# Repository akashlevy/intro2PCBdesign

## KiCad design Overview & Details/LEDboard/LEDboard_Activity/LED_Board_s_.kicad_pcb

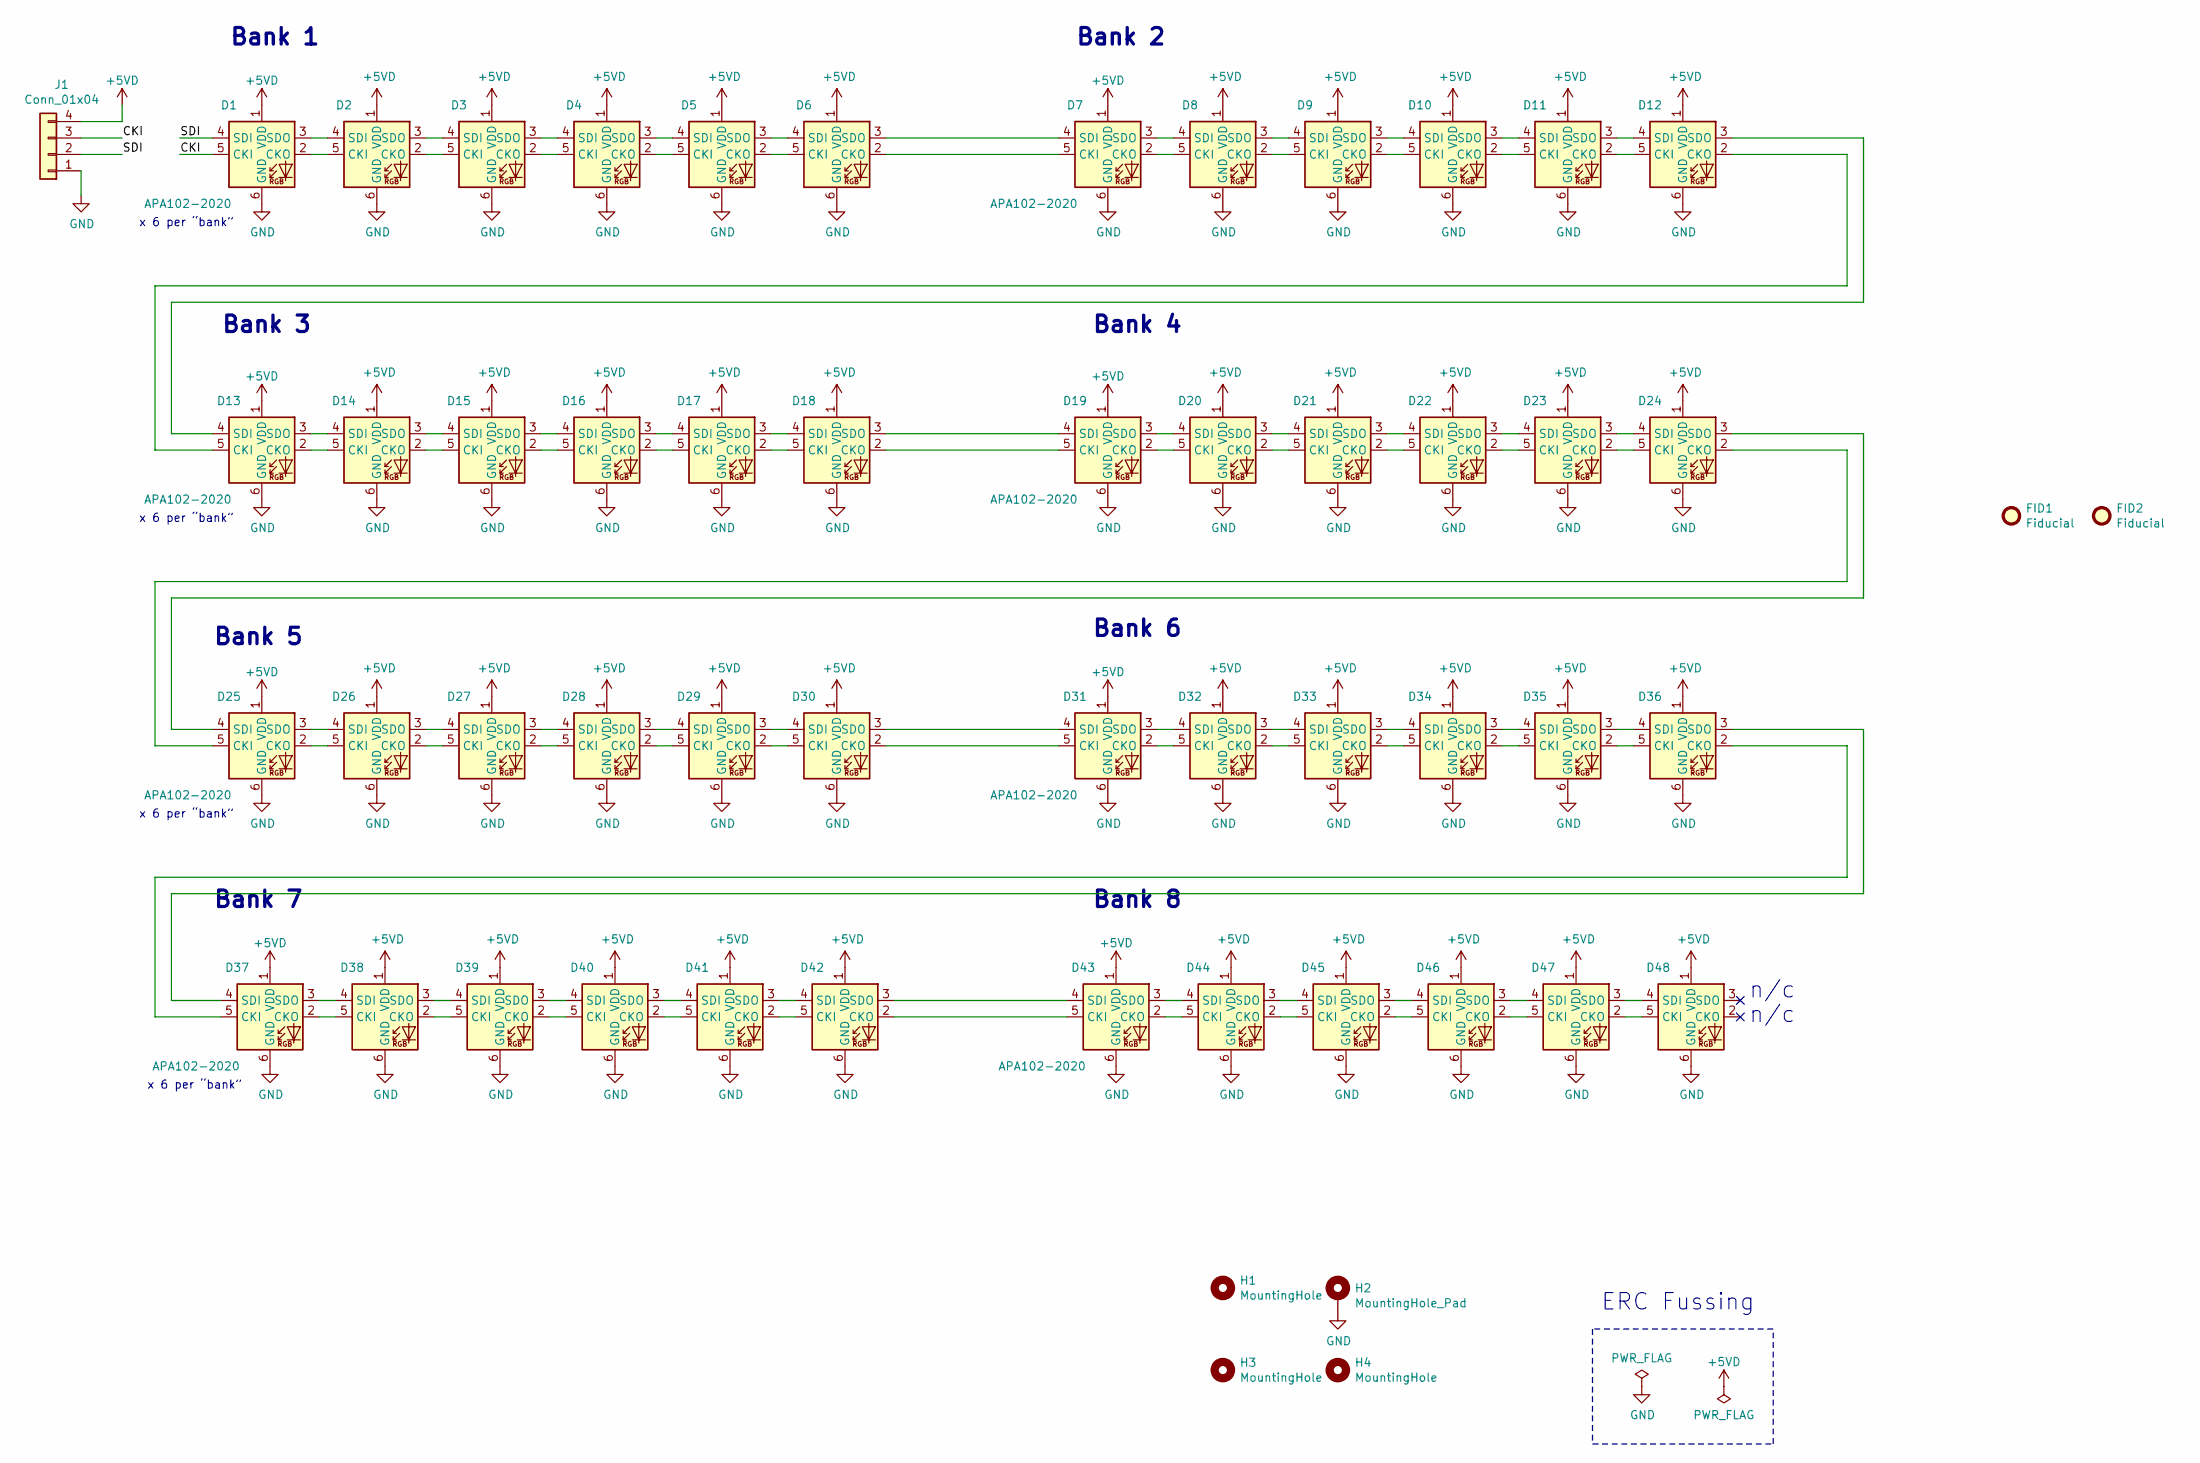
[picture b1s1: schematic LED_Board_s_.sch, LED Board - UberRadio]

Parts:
D1, D2, D3, D4, D5, D6, D7, D8, D9, D10, D11, D12, D13, D14, D15, D16, D17, D18, D19, D20, D21, D22, D23, D24, D25, D26, D27, D28, D29, D30, D31, D32, D33, D34, D35, D36, D37, D38, D39, D40, D41, D42, D43, D44, D45, D46, D47, D48: APA102-2020; LED-APA102-2020
FID1, FID2: Fiducial; Fiducial_0.5mm_Mask1mm
H1, H3, H4: MountingHole; MountingHole_3.5mm_Pad
H2: MountingHole_Pad; MountingHole_3.5mm_Pad_Via
J1: Conn_01x04; PinHeader_1x04_P2.54mm_Vertical

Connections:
+5VD: D1.1 (VDD), D2.1 (VDD), D3.1 (VDD), D4.1 (VDD), D5.1 (VDD), D6.1 (VDD), D7.1 (VDD), D8.1 (VDD), D9.1 (VDD), D10.1 (VDD), D11.1 (VDD), D12.1 (VDD), D13.1 (VDD), D14.1 (VDD), D15.1 (VDD), D16.1 (VDD), D17.1 (VDD), D18.1 (VDD), D19.1 (VDD), D20.1 (VDD), D21.1 (VDD), D22.1 (VDD), D23.1 (VDD), D24.1 (VDD), D25.1 (VDD), D26.1 (VDD), D27.1 (VDD), D28.1 (VDD), D29.1 (VDD), D30.1 (VDD), D31.1 (VDD), D32.1 (VDD), D33.1 (VDD), D34.1 (VDD), D35.1 (VDD), D36.1 (VDD), D37.1 (VDD), D38.1 (VDD), D39.1 (VDD), D40.1 (VDD), D41.1 (VDD), D42.1 (VDD), D43.1 (VDD), D44.1 (VDD), D45.1 (VDD), D46.1 (VDD), D47.1 (VDD), D48.1 (VDD), J1.4
/CKI: D1.5 (CKI), J1.3
/SDI: D1.4 (SDI), J1.2
GND: D1.6 (GND), D2.6 (GND), D3.6 (GND), D4.6 (GND), D5.6 (GND), D6.6 (GND), D7.6 (GND), D8.6 (GND), D9.6 (GND), D10.6 (GND), D11.6 (GND), D12.6 (GND), D13.6 (GND), D14.6 (GND), D15.6 (GND), D16.6 (GND), D17.6 (GND), D18.6 (GND), D19.6 (GND), D20.6 (GND), D21.6 (GND), D22.6 (GND), D23.6 (GND), D24.6 (GND), D25.6 (GND), D26.6 (GND), D27.6 (GND), D28.6 (GND), D29.6 (GND), D30.6 (GND), D31.6 (GND), D32.6 (GND), D33.6 (GND), D34.6 (GND), D35.6 (GND), D36.6 (GND), D37.6 (GND), D38.6 (GND), D39.6 (GND), D40.6 (GND), D41.6 (GND), D42.6 (GND), D43.6 (GND), D44.6 (GND), D45.6 (GND), D46.6 (GND), D47.6 (GND), D48.6 (GND), H2.1, H3.1, J1.1
unnamed: D1.2 (CKO), D2.5 (CKI)
unnamed: D1.3 (SDO), D2.4 (SDI)
unnamed: D2.2 (CKO), D3.5 (CKI)
unnamed: D2.3 (SDO), D3.4 (SDI)
unnamed: D3.2 (CKO), D4.5 (CKI)
unnamed: D3.3 (SDO), D4.4 (SDI)
unnamed: D4.2 (CKO), D5.5 (CKI)
unnamed: D4.3 (SDO), D5.4 (SDI)
unnamed: D5.2 (CKO), D6.5 (CKI)
unnamed: D5.3 (SDO), D6.4 (SDI)
unnamed: D6.2 (CKO), D7.5 (CKI)
unnamed: D6.3 (SDO), D7.4 (SDI)
unnamed: D7.2 (CKO), D8.5 (CKI)
unnamed: D7.3 (SDO), D8.4 (SDI)
unnamed: D8.2 (CKO), D9.5 (CKI)
unnamed: D8.3 (SDO), D9.4 (SDI)
unnamed: D10.2 (CKO), D11.5 (CKI)
unnamed: D10.3 (SDO), D11.4 (SDI)
unnamed: D9.3 (SDO), D10.4 (SDI)
unnamed: D9.2 (CKO), D10.5 (CKI)
unnamed: D11.2 (CKO), D12.5 (CKI)
unnamed: D11.3 (SDO), D12.4 (SDI)
unnamed: D12.2 (CKO), D13.5 (CKI)
unnamed: D12.3 (SDO), D13.4 (SDI)
unnamed: D13.2 (CKO), D14.5 (CKI)
unnamed: D13.3 (SDO), D14.4 (SDI)
unnamed: D14.2 (CKO), D15.5 (CKI)
unnamed: D14.3 (SDO), D15.4 (SDI)
unnamed: D15.2 (CKO), D16.5 (CKI)
unnamed: D15.3 (SDO), D16.4 (SDI)
unnamed: D16.2 (CKO), D17.5 (CKI)
unnamed: D16.3 (SDO), D17.4 (SDI)
unnamed: D17.2 (CKO), D18.5 (CKI)
unnamed: D17.3 (SDO), D18.4 (SDI)
unnamed: D18.2 (CKO), D19.5 (CKI)
unnamed: D18.3 (SDO), D19.4 (SDI)
unnamed: D19.2 (CKO), D20.5 (CKI)
unnamed: D19.3 (SDO), D20.4 (SDI)
unnamed: D20.2 (CKO), D21.5 (CKI)
unnamed: D20.3 (SDO), D21.4 (SDI)
unnamed: D21.2 (CKO), D22.5 (CKI)
unnamed: D21.3 (SDO), D22.4 (SDI)
unnamed: D22.2 (CKO), D23.5 (CKI)
unnamed: D22.3 (SDO), D23.4 (SDI)
unnamed: D23.2 (CKO), D24.5 (CKI)
unnamed: D23.3 (SDO), D24.4 (SDI)
unnamed: D24.2 (CKO), D25.5 (CKI)
unnamed: D24.3 (SDO), D25.4 (SDI)
unnamed: D25.2 (CKO), D26.5 (CKI)
unnamed: D25.3 (SDO), D26.4 (SDI)
unnamed: D26.2 (CKO), D27.5 (CKI)
unnamed: D26.3 (SDO), D27.4 (SDI)
unnamed: D27.2 (CKO), D28.5 (CKI)
unnamed: D27.3 (SDO), D28.4 (SDI)
unnamed: D28.2 (CKO), D29.5 (CKI)
unnamed: D28.3 (SDO), D29.4 (SDI)
unnamed: D29.2 (CKO), D30.5 (CKI)
unnamed: D29.3 (SDO), D30.4 (SDI)
unnamed: D30.2 (CKO), D31.5 (CKI)
unnamed: D30.3 (SDO), D31.4 (SDI)
unnamed: D31.2 (CKO), D32.5 (CKI)
unnamed: D31.3 (SDO), D32.4 (SDI)
unnamed: D32.2 (CKO), D33.5 (CKI)
unnamed: D32.3 (SDO), D33.4 (SDI)
unnamed: D33.2 (CKO), D34.5 (CKI)
unnamed: D33.3 (SDO), D34.4 (SDI)
unnamed: D34.2 (CKO), D35.5 (CKI)
unnamed: D34.3 (SDO), D35.4 (SDI)
unnamed: D35.2 (CKO), D36.5 (CKI)
unnamed: D35.3 (SDO), D36.4 (SDI)
unnamed: D36.2 (CKO), D37.5 (CKI)
unnamed: D36.3 (SDO), D37.4 (SDI)
unnamed: D37.2 (CKO), D38.5 (CKI)
unnamed: D37.3 (SDO), D38.4 (SDI)
unnamed: D38.2 (CKO), D39.5 (CKI)
unnamed: D38.3 (SDO), D39.4 (SDI)
unnamed: D39.2 (CKO), D40.5 (CKI)
unnamed: D39.3 (SDO), D40.4 (SDI)
unnamed: D40.2 (CKO), D41.5 (CKI)
unnamed: D40.3 (SDO), D41.4 (SDI)
unnamed: D41.2 (CKO), D42.5 (CKI)
unnamed: D41.3 (SDO), D42.4 (SDI)
unnamed: D42.2 (CKO), D43.5 (CKI)
unnamed: D42.3 (SDO), D43.4 (SDI)
unnamed: D43.2 (CKO), D44.5 (CKI)
unnamed: D43.3 (SDO), D44.4 (SDI)
unnamed: D44.2 (CKO), D45.5 (CKI)
unnamed: D44.3 (SDO), D45.4 (SDI)
unnamed: D45.2 (CKO), D46.5 (CKI)
unnamed: D45.3 (SDO), D46.4 (SDI)
unnamed: D46.2 (CKO), D47.5 (CKI)
unnamed: D46.3 (SDO), D47.4 (SDI)
unnamed: D47.2 (CKO), D48.5 (CKI)
unnamed: D47.3 (SDO), D48.4 (SDI)

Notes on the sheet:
x 6 per “bank”
Bank 1
Bank 2
Bank 3
Bank 5
Bank 7
Bank 4
Bank 6
Bank 8
ERC Fussing
n/c

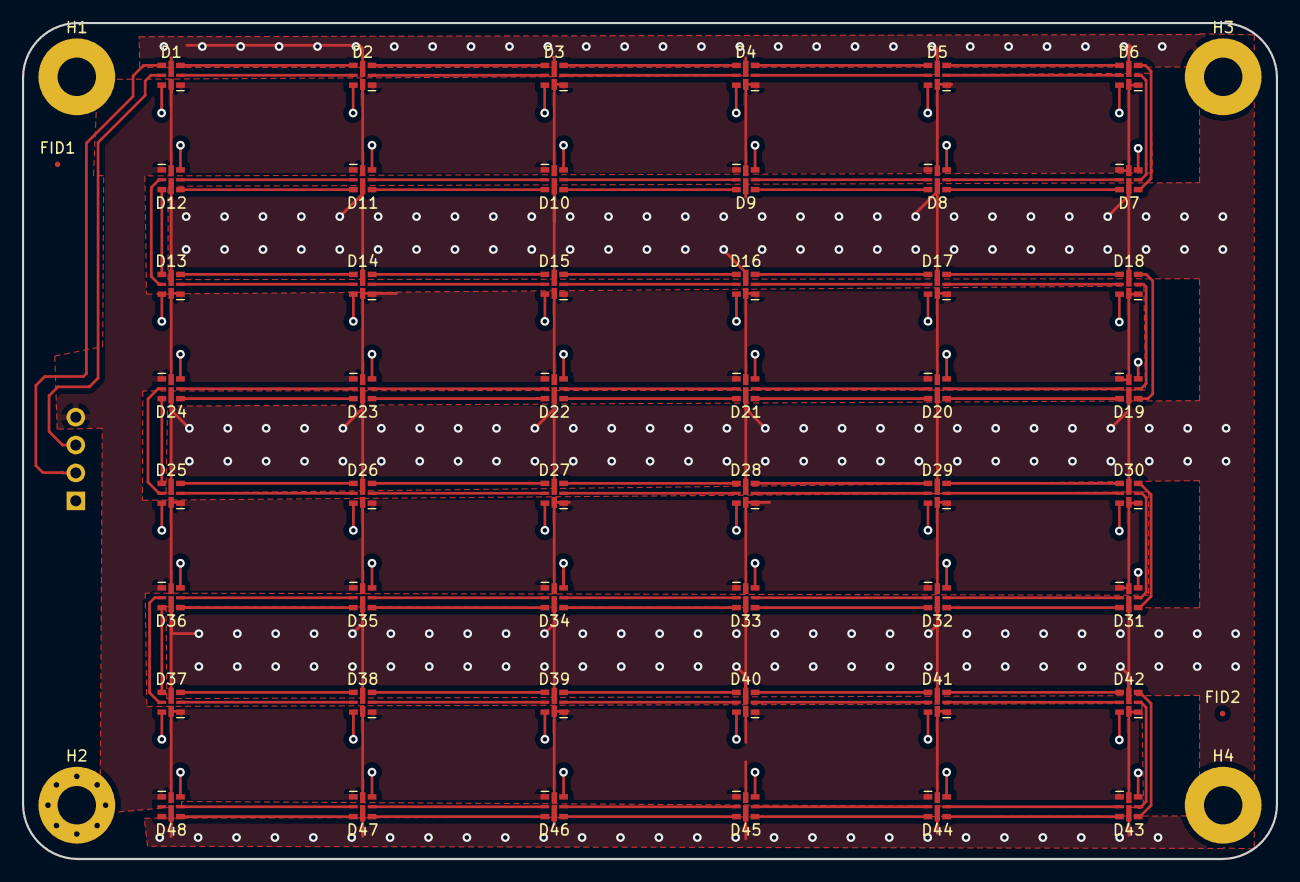
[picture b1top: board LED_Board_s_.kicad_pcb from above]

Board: 2 copper layers, 114.3 x 76.2 mm, 55 parts (1 on the bottom side), 98 nets.

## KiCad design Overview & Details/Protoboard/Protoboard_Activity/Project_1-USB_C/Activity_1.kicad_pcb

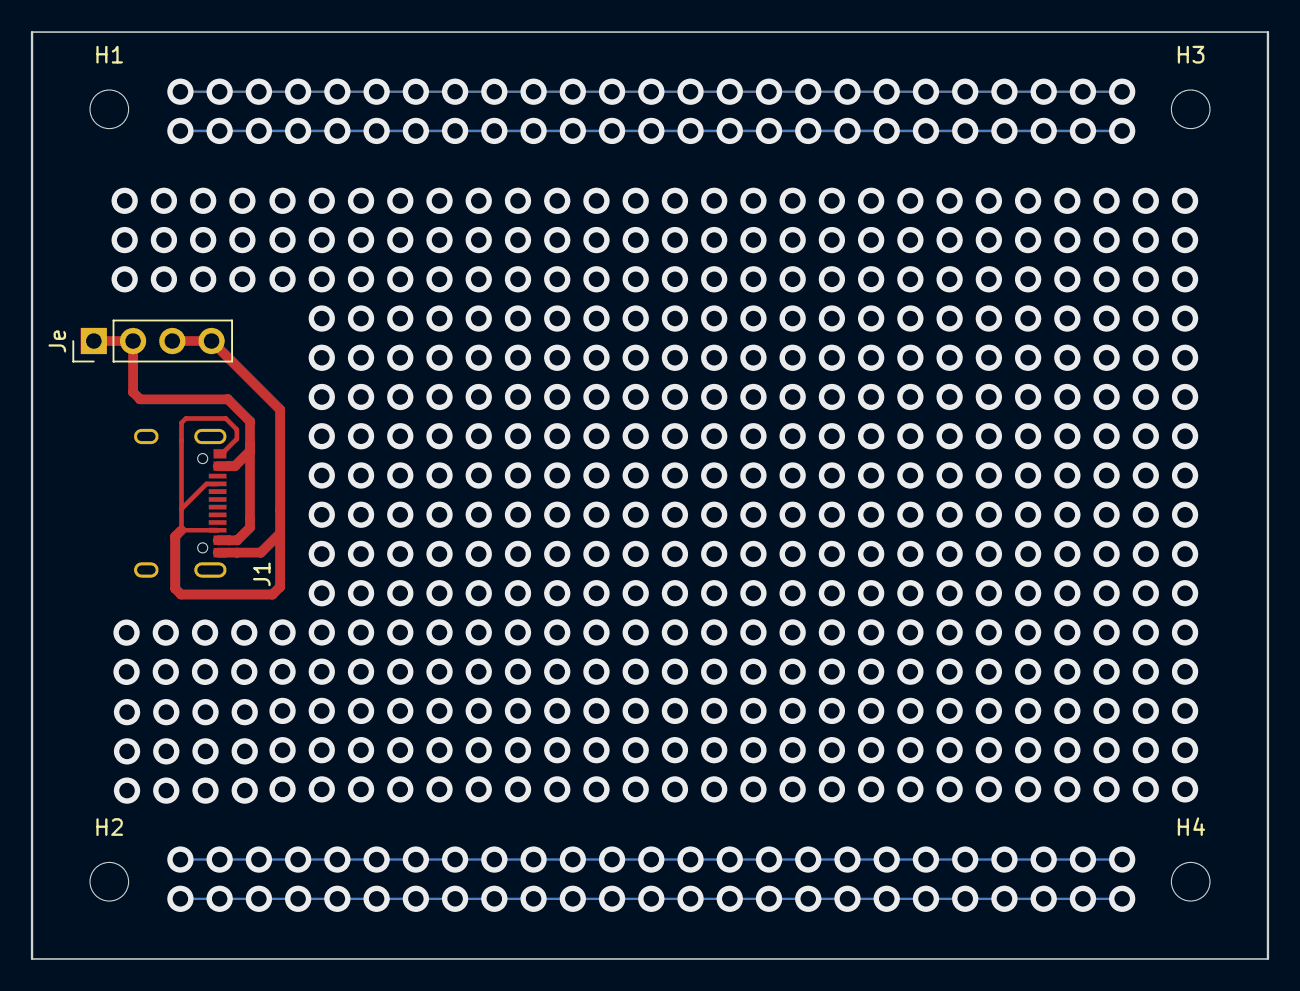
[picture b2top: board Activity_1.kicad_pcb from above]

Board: 2 copper layers, 80.0 x 60.0 mm, 6 parts (0 on the bottom side), 2 nets.

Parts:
H1, H2, H3, H4: MountingHole; MountingHole_2.5mm
J1: USB_C; USB_C_Receptacle_XKB_U262-161N-4BVC11
Je: Conn_01x04; PinHeader_1x04_P2.54mm_Vertical

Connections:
/+5: J1.A4, J1.A9, Je.1, Je.2
unnamed: J1.A1, J1.A5, J1.A12, J1.B5, Je.3, Je.4

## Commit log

2020-04-15 Activity 1
2020-04-15 Move stuff
2020-04-28 project1
2020-05-04 LED board fixes
2020-05-07 Updates to power boarcd
